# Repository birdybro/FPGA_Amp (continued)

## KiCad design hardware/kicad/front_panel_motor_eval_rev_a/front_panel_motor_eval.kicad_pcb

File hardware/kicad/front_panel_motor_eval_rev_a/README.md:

# Motor-volume evaluation PCB — revision A

This is the first physical KiCad design derived from the product hardware
specification. It isolates the electrically noisy and mechanically uncertain
motor-volume subsystem so it can be measured before committing it to the large
LCD/MCU front-panel board.

Open `front_panel_motor_eval.kicad_pro` in KiCad 10. The checked board was
generated and verified with KiCad 10.0.5. KiCad does not live-reload files
changed by the generator, so close and reopen the schematic/PCB editor after an
external regeneration. Do not hand-edit generated connectivity without also
updating `generate.py`.

## Verified artifact

The checked-in board is an 80 x 48 mm, four-copper-layer EVT daughterboard with
44 schematic parts, four M3 mounting holes, 28 named nets, 235 routed segments,
and 28 vias. The last clean run reports:

```text
schematic ERC violations:  0
PCB DRC violations:        0
unconnected PCB items:     0
minimum routed width:      0.25 mm
minimum via drill:         0.35 mm
```

The bottom and inner-1 layers are GND pours. Inner-2 is reserved as `POWER` but
is not used as an indiscriminate plane in this small prototype. Connector and
test-point functions are labeled on silkscreen. R19/C10 carry KiCad DNP flags,
and placement export excludes them.

## Electrical intent

- 4.75–5.25 V motor input for the Bourns PRM16 4.5 V / 100 mA prototype motor.
- DRV8874 in PH/EN control mode with 33 ohm input damping and 100 kilohm
  fail-off pulldowns.
- 10 kilohm IPROPI resistor: nominal 0.45 V at 100 mA using the datasheet's
  nominal 450 microamp/amp scaling. This is stall telemetry, not precision
  metrology; the datasheet permits substantial absolute error below 0.4 A.
- 14.7/10 kilohm VREF divider and 10 kilohm IPROPI resistor: nominal hardware
  current regulation near 297 mA. This threshold and the 500 mA PTC are not
  released values until motor start/stall measurements are complete.
- IMODE uses 62 kilohms to select cycle-by-cycle regulation and latched-off
  overcurrent behavior. Firmware still detects ordinary stalls from IPROPI and
  stops without waiting for device OCP.
- Dual 10 kilohm-class potentiometer tracks are excited ratiometrically from
  MCU 3.3 V. Their filtered wipers carry position only and never audio.
- R19/C10 are deliberately DNP EMI-tuning sites. They may only be populated
  from measured motor emissions and driver-current evidence.

## Connectors

`J1` is keyed motor power. `J2` is the prototype MCU interface. `J3` is a
separate twisted motor pair. `J4` carries the two position tracks. Separating
J3 from J4 prevents PWM current from sharing position-sensor conductors.

This is an EVT instrument, not a production-released board. The PRM16 has a
published 15,000-cycle rotational life, while the product requirement remains
100,000 qualified full-range cycles.

The DRV8874 PowerPAD is assigned to GND using the standard non-via-in-pad KiCad
HTSSOP footprint. That is suitable for low-current motor evaluation only after
assembly inspection; a production layout must close copper area, thermal vias,
paste aperture, and fabricator capability from measured dissipation. The
0.25 mm routes are ample for the candidate's published 100 mA maximum motor
current but are not evidence for an unselected larger mechanism. Connector
families, PTC trip/hold rating, TVS selection, current threshold, and optional
snubber remain provisional until bench measurements.

Primary component references are the
[TI DRV8874 datasheet](https://www.ti.com/lit/ds/symlink/drv8874.pdf) and the
[Bourns PRM16 datasheet](https://www.bourns.com/docs/product-datasheets/PRM16.pdf).
The route was produced with
[Freerouting](https://github.com/freerouting/freerouting) v2.2.4 through
KiCad's DSN/SES interchange. Freerouting is intentionally not vendored.

## Commands

```text
make kicad-motor-generate
make kicad-motor-route FREEROUTING_JAR=/path/to/freerouting.jar
make kicad-motor-check
make kicad-motor-fab
```

`kicad-motor-route` starts from generated placement and can occasionally leave
an unrouted item because the open autorouter is heuristic. The mandatory check
target fails in that case; rerun the route rather than accepting an incomplete
board. Fabrication outputs are generated under
`build/kicad/front_panel_motor_eval/fab/` and are intentionally not committed.
Passing export is not an instruction to order boards: peer layout review,
mechanical fit, sourcing, assembly rules, and the provisional items above are
still open.

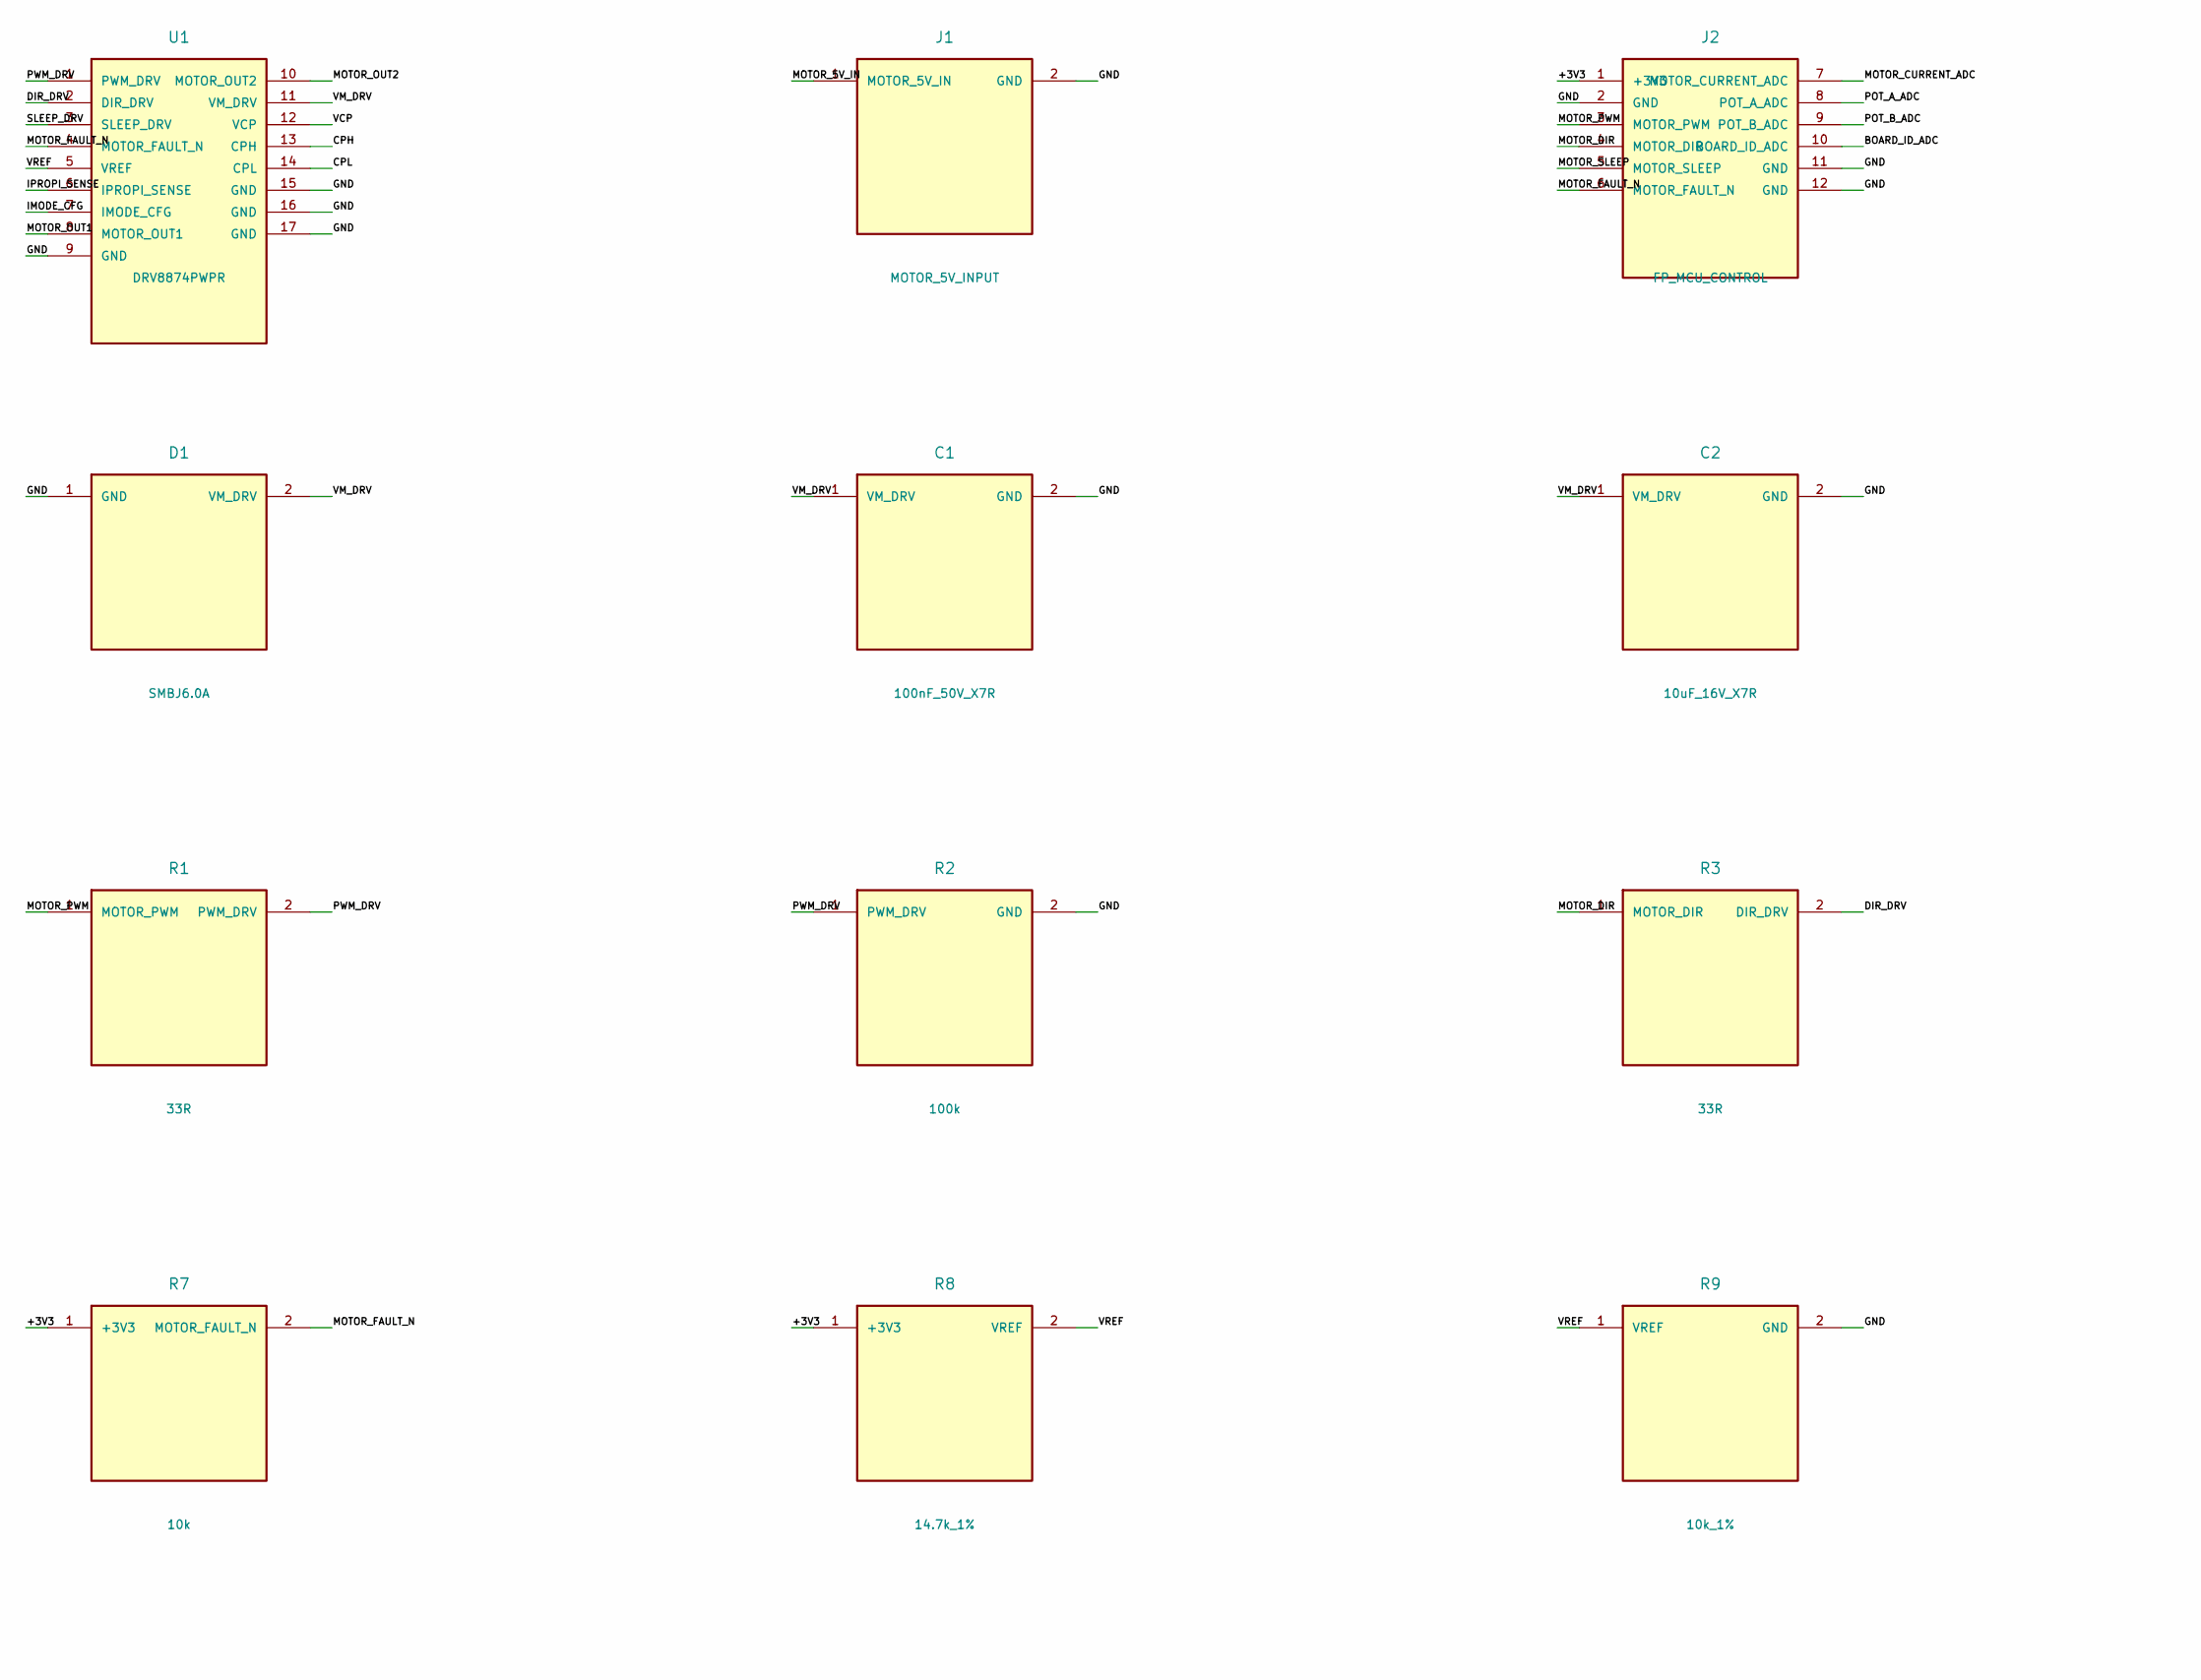
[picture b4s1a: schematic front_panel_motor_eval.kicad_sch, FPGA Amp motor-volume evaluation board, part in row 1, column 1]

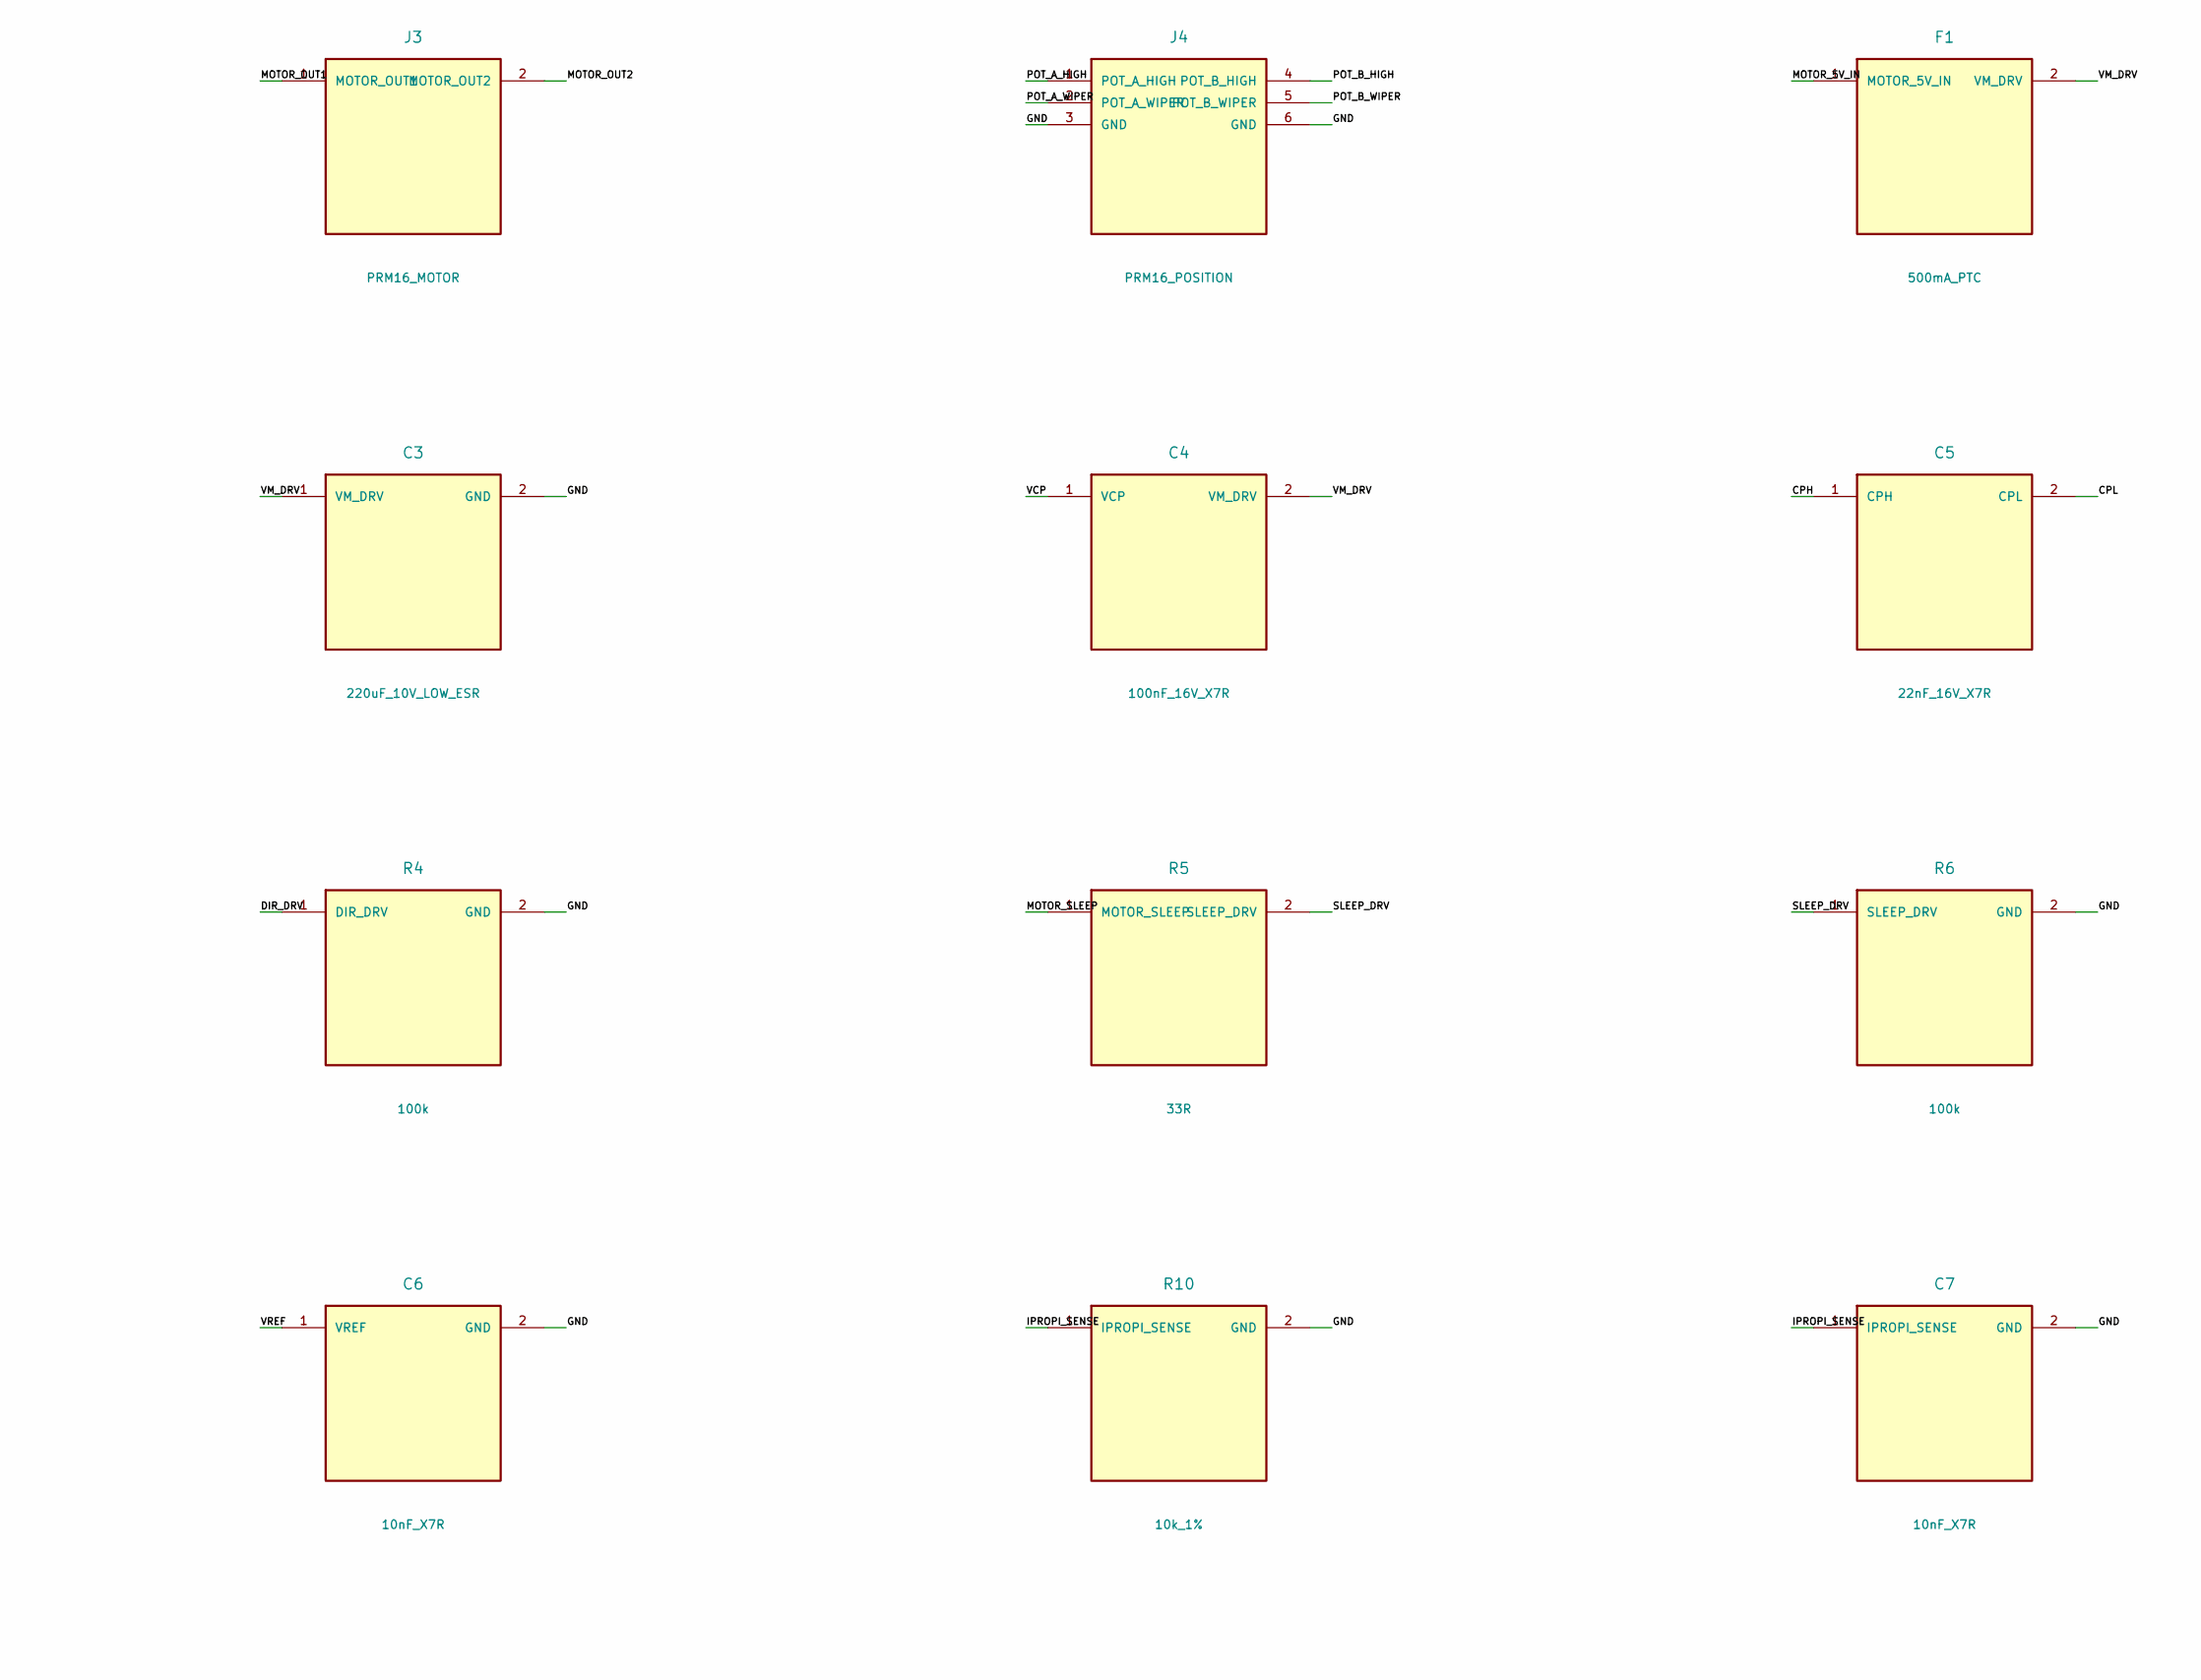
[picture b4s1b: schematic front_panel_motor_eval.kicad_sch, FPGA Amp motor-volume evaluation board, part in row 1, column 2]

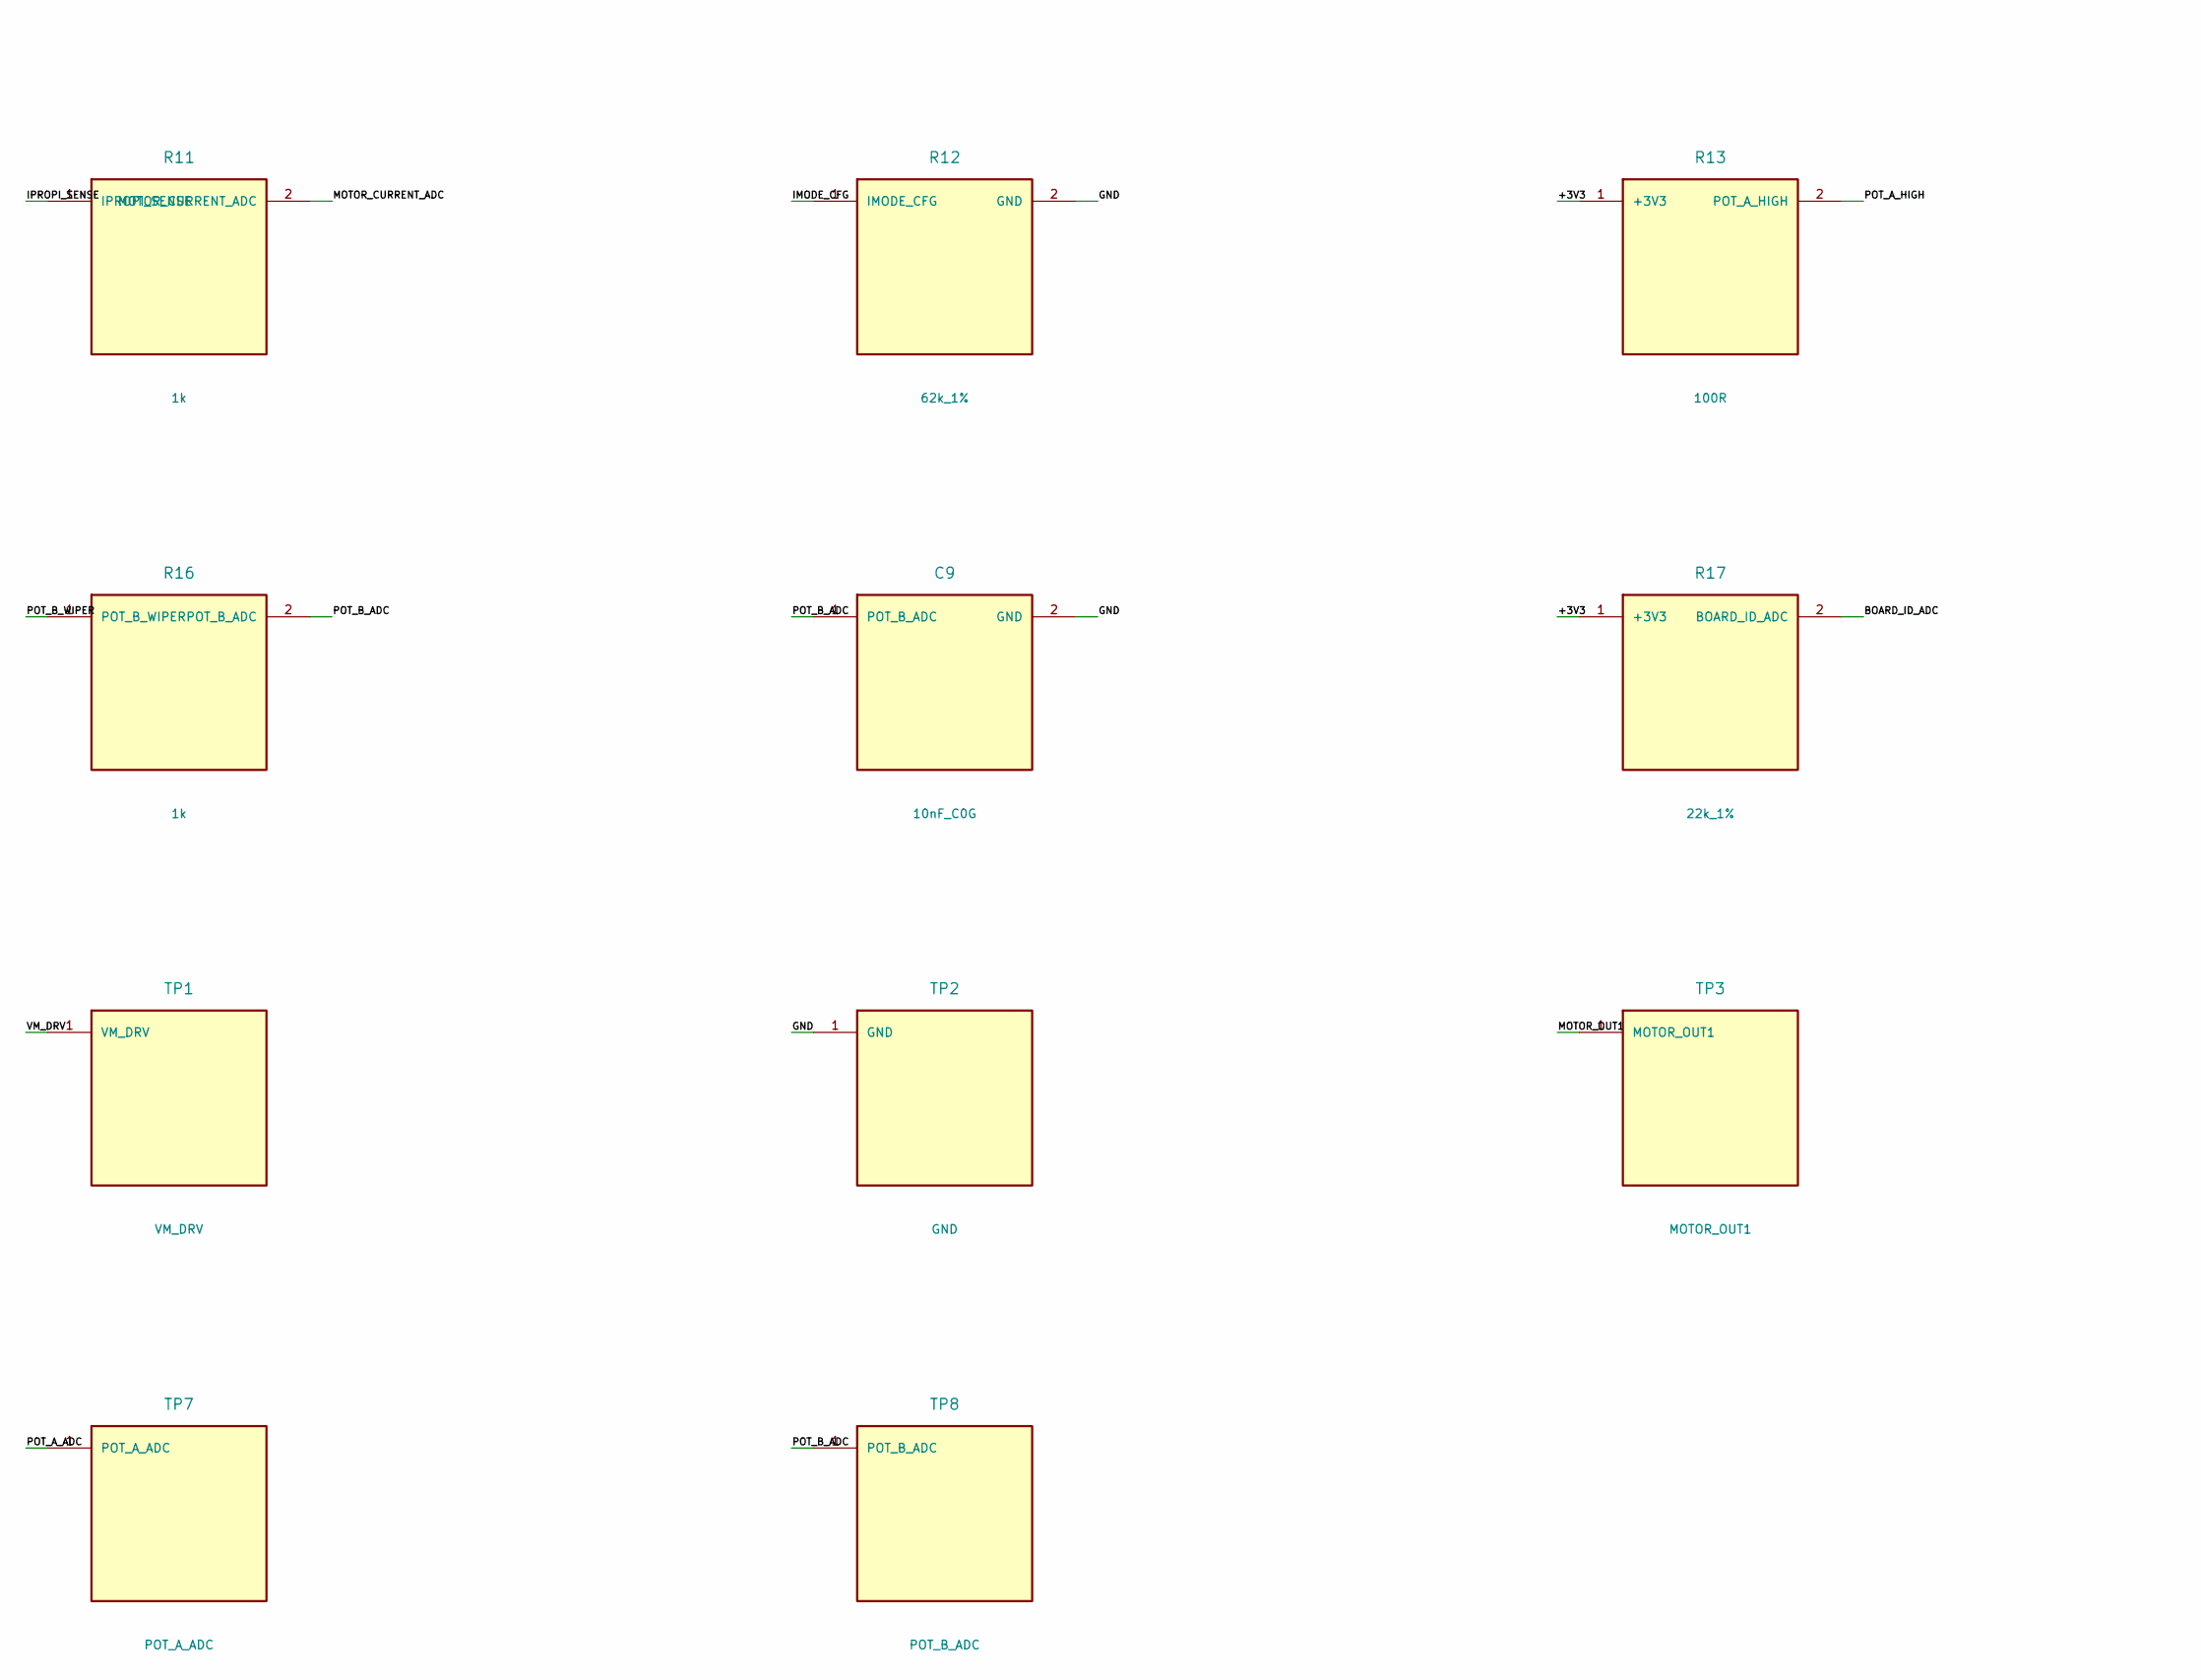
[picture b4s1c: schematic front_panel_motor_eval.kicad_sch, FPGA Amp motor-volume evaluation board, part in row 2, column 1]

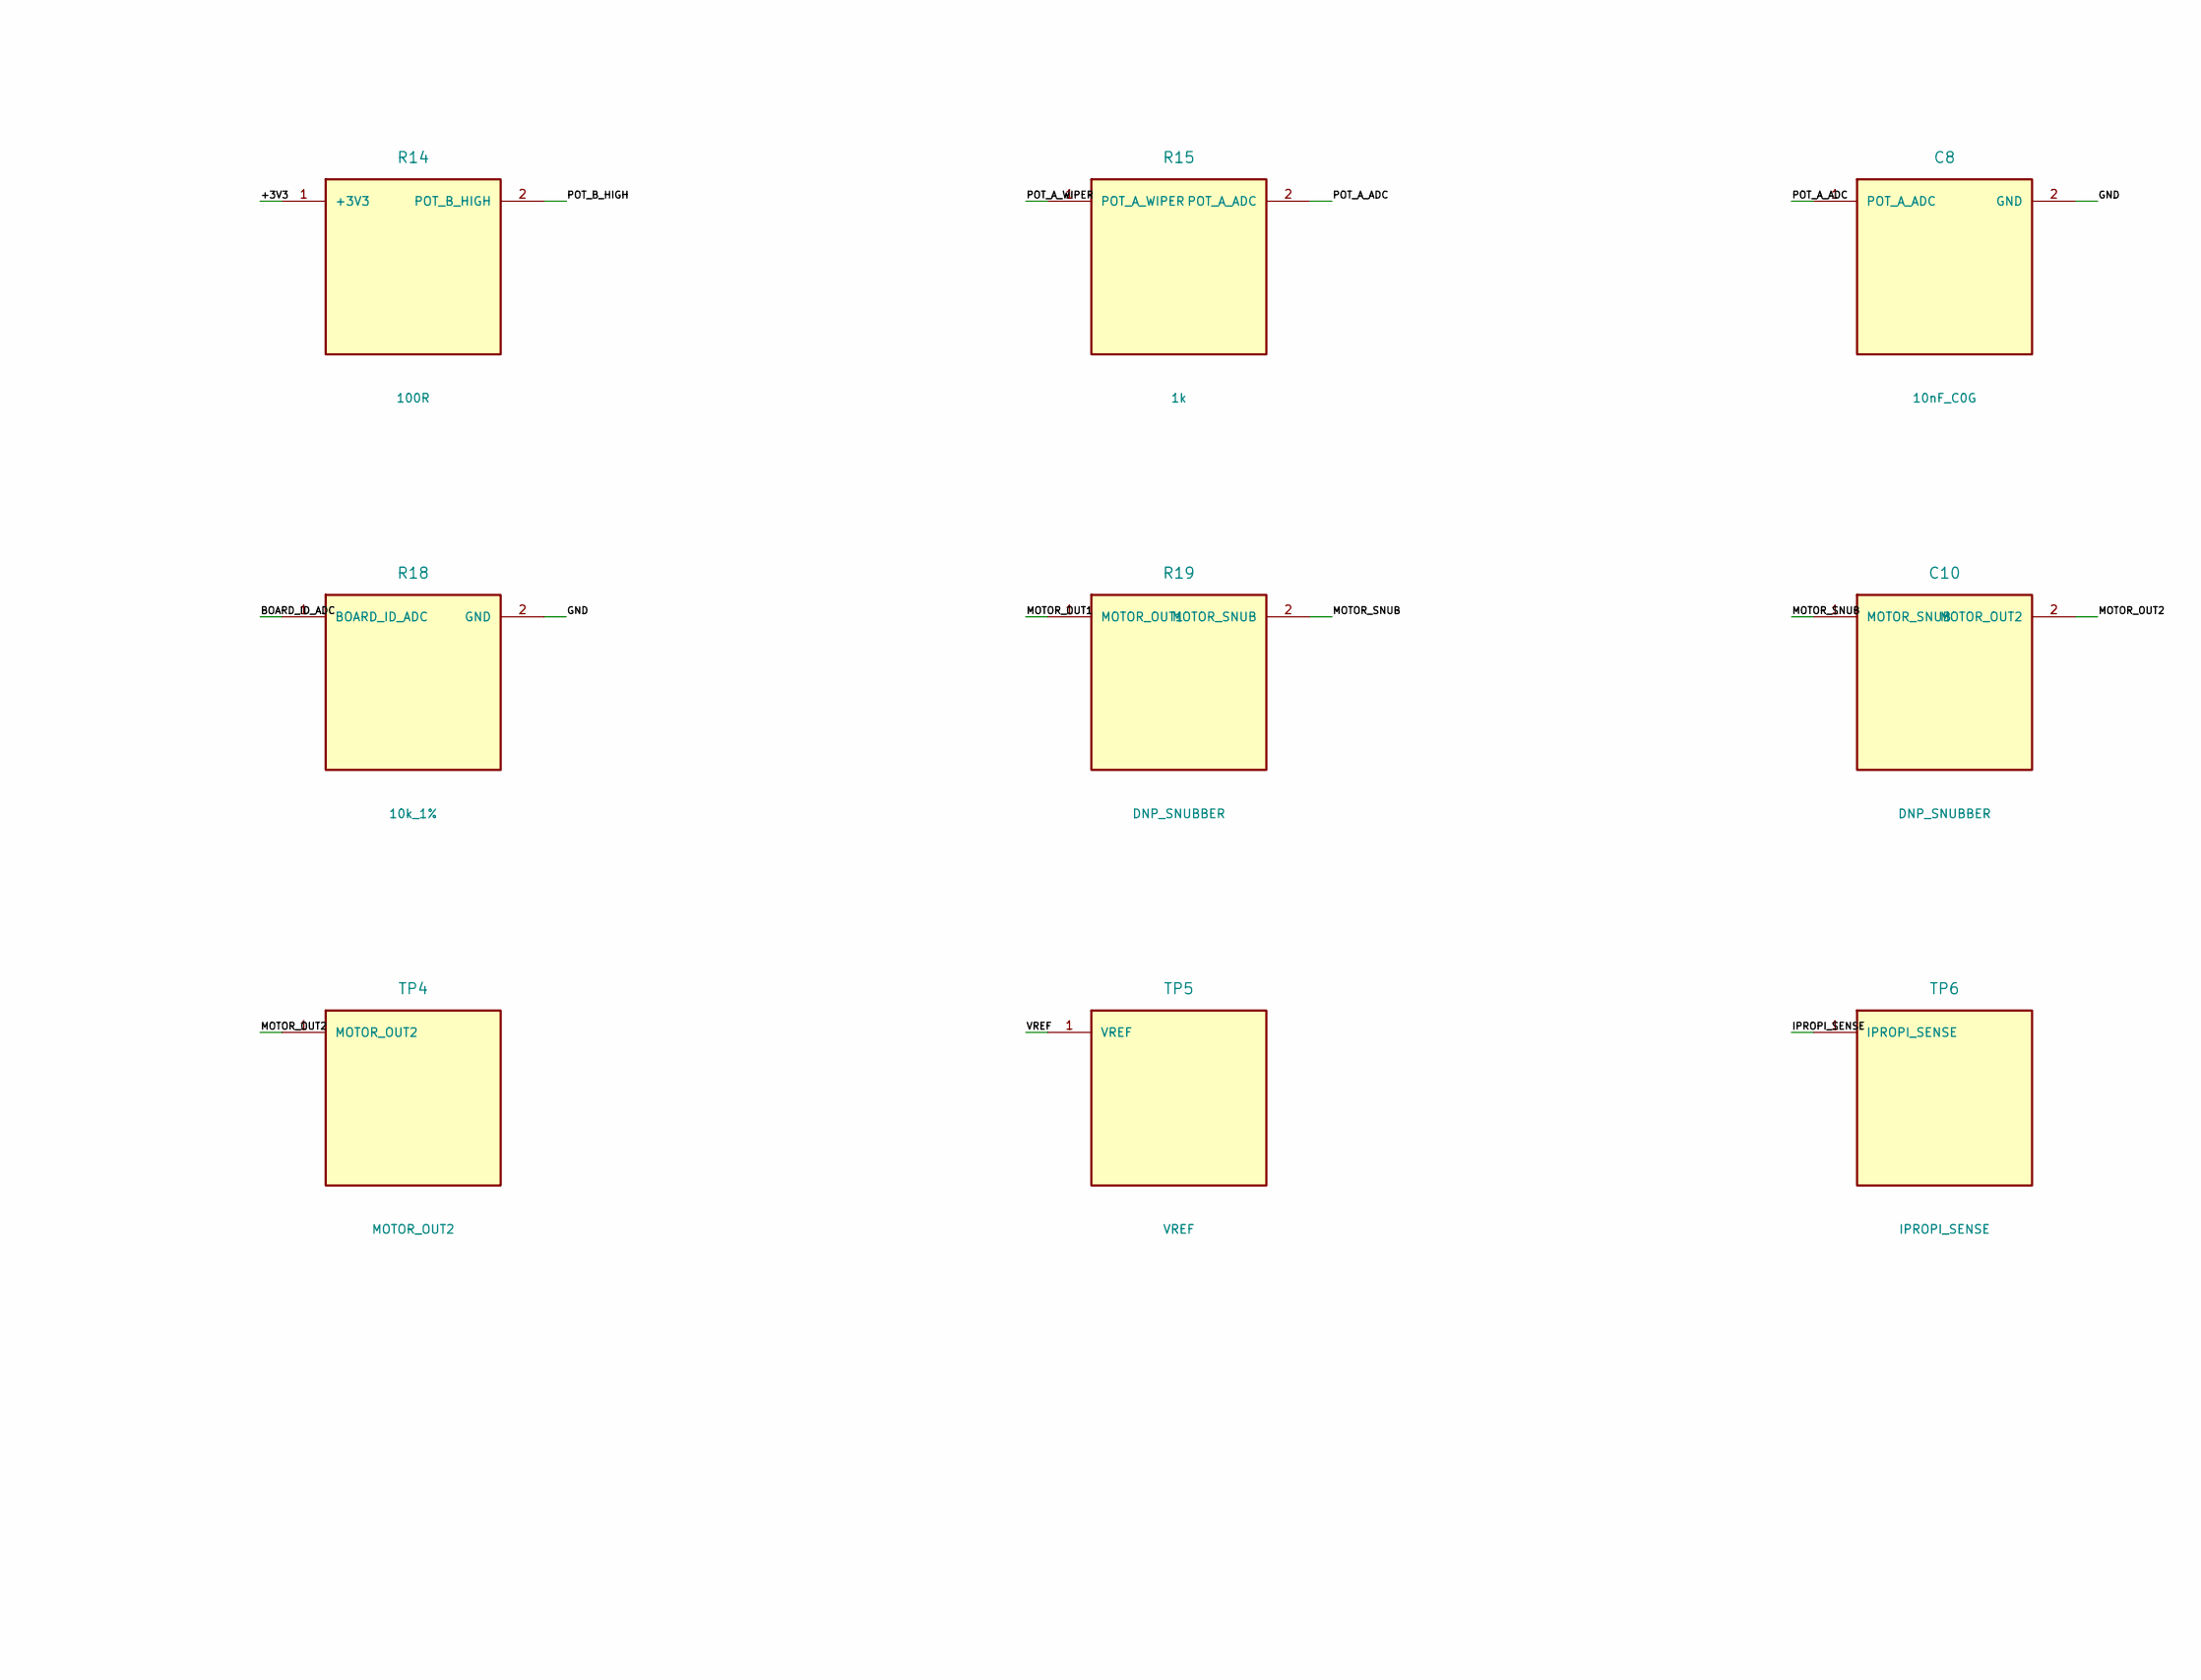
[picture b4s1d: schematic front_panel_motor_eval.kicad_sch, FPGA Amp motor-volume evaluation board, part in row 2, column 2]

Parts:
C1: 100nF_50V_X7R; C_0805_2012Metric
C2: 10uF_16V_X7R; C_1210_3225Metric
C3: 220uF_10V_LOW_ESR; C_Elec_6.3x5.8
C4: 100nF_16V_X7R; C_0805_2012Metric
C5: 22nF_16V_X7R; C_0805_2012Metric
C6, C7: 10nF_X7R; C_0805_2012Metric
C8, C9: 10nF_C0G; C_0805_2012Metric
C10: DNP_SNUBBER; C_0805_2012Metric
D1: SMBJ6.0A; D_SMB
F1: 500mA_PTC; Fuse_1206_3216Metric
J1: MOTOR_5V_INPUT; JST_VH_B2P-VH-B_1x02_P3.96mm_Vertical
J2: FP_MCU_CONTROL; PinHeader_2x06_P2.54mm_Vertical
J3: PRM16_MOTOR; JST_VH_B2P-VH-B_1x02_P3.96mm_Vertical
J4: PRM16_POSITION; JST_XH_B6B-XH-A_1x06_P2.50mm_Vertical
R1, R3, R5: 33R; R_0805_2012Metric
R2, R4, R6: 100k; R_0805_2012Metric
R7: 10k; R_0805_2012Metric
R8: 14.7k_1%; R_0805_2012Metric
R9, R10, R18: 10k_1%; R_0805_2012Metric
R11, R15, R16: 1k; R_0805_2012Metric
R12: 62k_1%; R_0805_2012Metric
R13, R14: 100R; R_0805_2012Metric
R17: 22k_1%; R_0805_2012Metric
R19: DNP_SNUBBER; R_0805_2012Metric
TP1: VM_DRV; TestPoint_Plated_Hole_D2.0mm
TP2: GND; TestPoint_Plated_Hole_D2.0mm
TP3: MOTOR_OUT1; TestPoint_Plated_Hole_D2.0mm
TP4: MOTOR_OUT2; TestPoint_Plated_Hole_D2.0mm
TP5: VREF; TestPoint_Plated_Hole_D2.0mm
TP6: IPROPI_SENSE; TestPoint_Plated_Hole_D2.0mm
TP7: POT_A_ADC; TestPoint_Plated_Hole_D2.0mm
TP8: POT_B_ADC; TestPoint_Plated_Hole_D2.0mm
U1: DRV8874PWPR; HTSSOP-16-1EP_4.4x5mm_P0.65mm_EP3.4x5mm_Mask2.46x2.31mm

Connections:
+3V3: J2.1 (+3V3), R7.1 (+3V3), R8.1 (+3V3), R13.1 (+3V3), R14.1 (+3V3), R17.1 (+3V3)
BOARD_ID_ADC: J2.10 (BOARD_ID_ADC), R17.2 (BOARD_ID_ADC), R18.1 (BOARD_ID_ADC)
CPH: C5.1 (CPH), U1.13 (CPH)
CPL: C5.2 (CPL), U1.14 (CPL)
DIR_DRV: R3.2 (DIR_DRV), R4.1 (DIR_DRV), U1.2 (DIR_DRV)
GND: C1.2 (GND), C2.2 (GND), C3.2 (GND), C6.2 (GND), C7.2 (GND), C8.2 (GND), C9.2 (GND), D1.1 (GND), J1.2 (GND), J2.2 (GND), J2.11 (GND), J2.12 (GND), J4.3 (GND), J4.6 (GND), R2.2 (GND), R4.2 (GND), R6.2 (GND), R9.2 (GND), R10.2 (GND), R12.2 (GND), R18.2 (GND), TP2.1, U1.9 (GND), U1.15 (GND), U1.16 (GND), U1.17 (GND)
IMODE_CFG: R12.1 (IMODE_CFG), U1.7 (IMODE_CFG)
IPROPI_SENSE: C7.1 (IPROPI_SENSE), R10.1 (IPROPI_SENSE), R11.1 (IPROPI_SENSE), TP6.1, U1.6 (IPROPI_SENSE)
MOTOR_5V_IN: F1.1 (MOTOR_5V_IN), J1.1 (MOTOR_5V_IN)
MOTOR_CURRENT_ADC: J2.7 (MOTOR_CURRENT_ADC), R11.2 (MOTOR_CURRENT_ADC)
MOTOR_DIR: J2.4 (MOTOR_DIR), R3.1 (MOTOR_DIR)
MOTOR_FAULT_N: J2.6 (MOTOR_FAULT_N), R7.2 (MOTOR_FAULT_N), U1.4 (MOTOR_FAULT_N)
MOTOR_OUT1: J3.1 (MOTOR_OUT1), R19.1 (MOTOR_OUT1), TP3.1, U1.8 (MOTOR_OUT1)
MOTOR_OUT2: C10.2 (MOTOR_OUT2), J3.2 (MOTOR_OUT2), TP4.1, U1.10 (MOTOR_OUT2)
MOTOR_PWM: J2.3 (MOTOR_PWM), R1.1 (MOTOR_PWM)
MOTOR_SLEEP: J2.5 (MOTOR_SLEEP), R5.1 (MOTOR_SLEEP)
MOTOR_SNUB: C10.1 (MOTOR_SNUB), R19.2 (MOTOR_SNUB)
POT_A_ADC: C8.1 (POT_A_ADC), J2.8 (POT_A_ADC), R15.2 (POT_A_ADC), TP7.1
POT_A_HIGH: J4.1 (POT_A_HIGH), R13.2 (POT_A_HIGH)
POT_A_WIPER: J4.2 (POT_A_WIPER), R15.1 (POT_A_WIPER)
POT_B_ADC: C9.1 (POT_B_ADC), J2.9 (POT_B_ADC), R16.2 (POT_B_ADC), TP8.1
POT_B_HIGH: J4.4 (POT_B_HIGH), R14.2 (POT_B_HIGH)
POT_B_WIPER: J4.5 (POT_B_WIPER), R16.1 (POT_B_WIPER)
PWM_DRV: R1.2 (PWM_DRV), R2.1 (PWM_DRV), U1.1 (PWM_DRV)
SLEEP_DRV: R5.2 (SLEEP_DRV), R6.1 (SLEEP_DRV), U1.3 (SLEEP_DRV)
VCP: C4.1 (VCP), U1.12 (VCP)
VM_DRV: C1.1 (VM_DRV), C2.1 (VM_DRV), C3.1 (VM_DRV), C4.2 (VM_DRV), D1.2 (VM_DRV), F1.2 (VM_DRV), TP1.1, U1.11 (VM_DRV)
VREF: C6.1 (VREF), R8.2 (VREF), R9.1 (VREF), TP5.1, U1.5 (VREF)

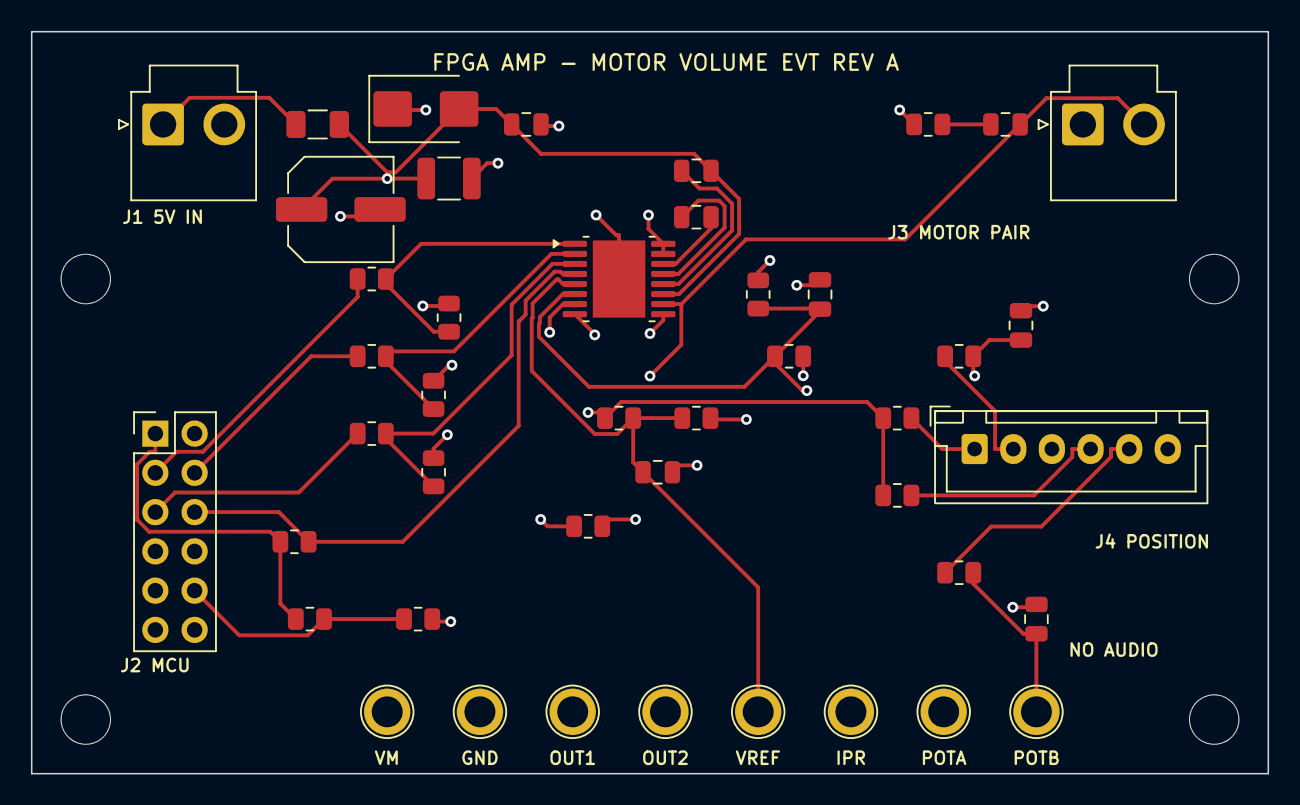
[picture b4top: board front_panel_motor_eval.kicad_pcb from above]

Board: 4 copper layers, 80.0 x 48.0 mm, 48 parts (0 on the bottom side), 28 nets.

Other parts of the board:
H1, H2, H3, H4: M3_CHASSIS; MountingHole_3.2mm_M3

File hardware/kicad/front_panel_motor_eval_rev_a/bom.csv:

Reference,Value,Footprint,Description
U1,DRV8874PWPR,Package_SO:HTSSOP-16-1EP_4.4x5mm_P0.65mm_EP3.4x5mm_Mask2.46x2.31mm,Current-sensed PH/EN H-bridge; PWP PowerPAD must be soldered
J1,MOTOR_5V_INPUT,Connector_JST:JST_VH_B2P-VH-B_1x02_P3.96mm_Vertical,Keyed 4.75-5.25 V motor supply from PB
J2,FP_MCU_CONTROL,Connector_PinHeader_2.54mm:PinHeader_2x06_P2.54mm_Vertical,MCU control/telemetry; prototype header; production connector TBD
J3,PRM16_MOTOR,Connector_JST:JST_VH_B2P-VH-B_1x02_P3.96mm_Vertical,Twisted motor pair to supported volume mechanism
J4,PRM16_POSITION,Connector_JST:JST_XH_B6B-XH-A_1x06_P2.50mm_Vertical,Two ratiometric position tracks; never carries audio
F1,500mA_PTC,Fuse:Fuse_1206_3216Metric,Resettable input fuse; select hold/trip after measured stall test
D1,SMBJ6.0A,Diode_SMD:D_SMB,Motor-rail transient clamp
C1,100nF_50V_X7R,Capacitor_SMD:C_0805_2012Metric,
C2,10uF_16V_X7R,Capacitor_SMD:C_1210_3225Metric,
C3,220uF_10V_LOW_ESR,Capacitor_SMD:C_Elec_6.3x5.8,
C4,100nF_16V_X7R,Capacitor_SMD:C_0805_2012Metric,
C5,22nF_16V_X7R,Capacitor_SMD:C_0805_2012Metric,
R1,33R,Resistor_SMD:R_0805_2012Metric,
R2,100k,Resistor_SMD:R_0805_2012Metric,
R3,33R,Resistor_SMD:R_0805_2012Metric,
R4,100k,Resistor_SMD:R_0805_2012Metric,
R5,33R,Resistor_SMD:R_0805_2012Metric,
R6,100k,Resistor_SMD:R_0805_2012Metric,
R7,10k,Resistor_SMD:R_0805_2012Metric,
R8,14.7k_1%,Resistor_SMD:R_0805_2012Metric,
R9,10k_1%,Resistor_SMD:R_0805_2012Metric,
C6,10nF_X7R,Capacitor_SMD:C_0805_2012Metric,
R10,10k_1%,Resistor_SMD:R_0805_2012Metric,
C7,10nF_X7R,Capacitor_SMD:C_0805_2012Metric,
R11,1k,Resistor_SMD:R_0805_2012Metric,
R12,62k_1%,Resistor_SMD:R_0805_2012Metric,
R13,100R,Resistor_SMD:R_0805_2012Metric,
R14,100R,Resistor_SMD:R_0805_2012Metric,
R15,1k,Resistor_SMD:R_0805_2012Metric,
C8,10nF_C0G,Capacitor_SMD:C_0805_2012Metric,
R16,1k,Resistor_SMD:R_0805_2012Metric,
C9,10nF_C0G,Capacitor_SMD:C_0805_2012Metric,
R17,22k_1%,Resistor_SMD:R_0805_2012Metric,
R18,10k_1%,Resistor_SMD:R_0805_2012Metric,
R19,DNP_SNUBBER,Resistor_SMD:R_0805_2012Metric,DNP; tune only from conducted/radiated measurements
C10,DNP_SNUBBER,Capacitor_SMD:C_0805_2012Metric,DNP; tune only from conducted/radiated measurements
TP1,VM_DRV,TestPoint:TestPoint_Plated_Hole_D2.0mm,Bring-up test point
TP2,GND,TestPoint:TestPoint_Plated_Hole_D2.0mm,Bring-up test point
TP3,MOTOR_OUT1,TestPoint:TestPoint_Plated_Hole_D2.0mm,Bring-up test point
TP4,MOTOR_OUT2,TestPoint:TestPoint_Plated_Hole_D2.0mm,Bring-up test point
TP5,VREF,TestPoint:TestPoint_Plated_Hole_D2.0mm,Bring-up test point
TP6,IPROPI_SENSE,TestPoint:TestPoint_Plated_Hole_D2.0mm,Bring-up test point
TP7,POT_A_ADC,TestPoint:TestPoint_Plated_Hole_D2.0mm,Bring-up test point
TP8,POT_B_ADC,TestPoint:TestPoint_Plated_Hole_D2.0mm,Bring-up test point
